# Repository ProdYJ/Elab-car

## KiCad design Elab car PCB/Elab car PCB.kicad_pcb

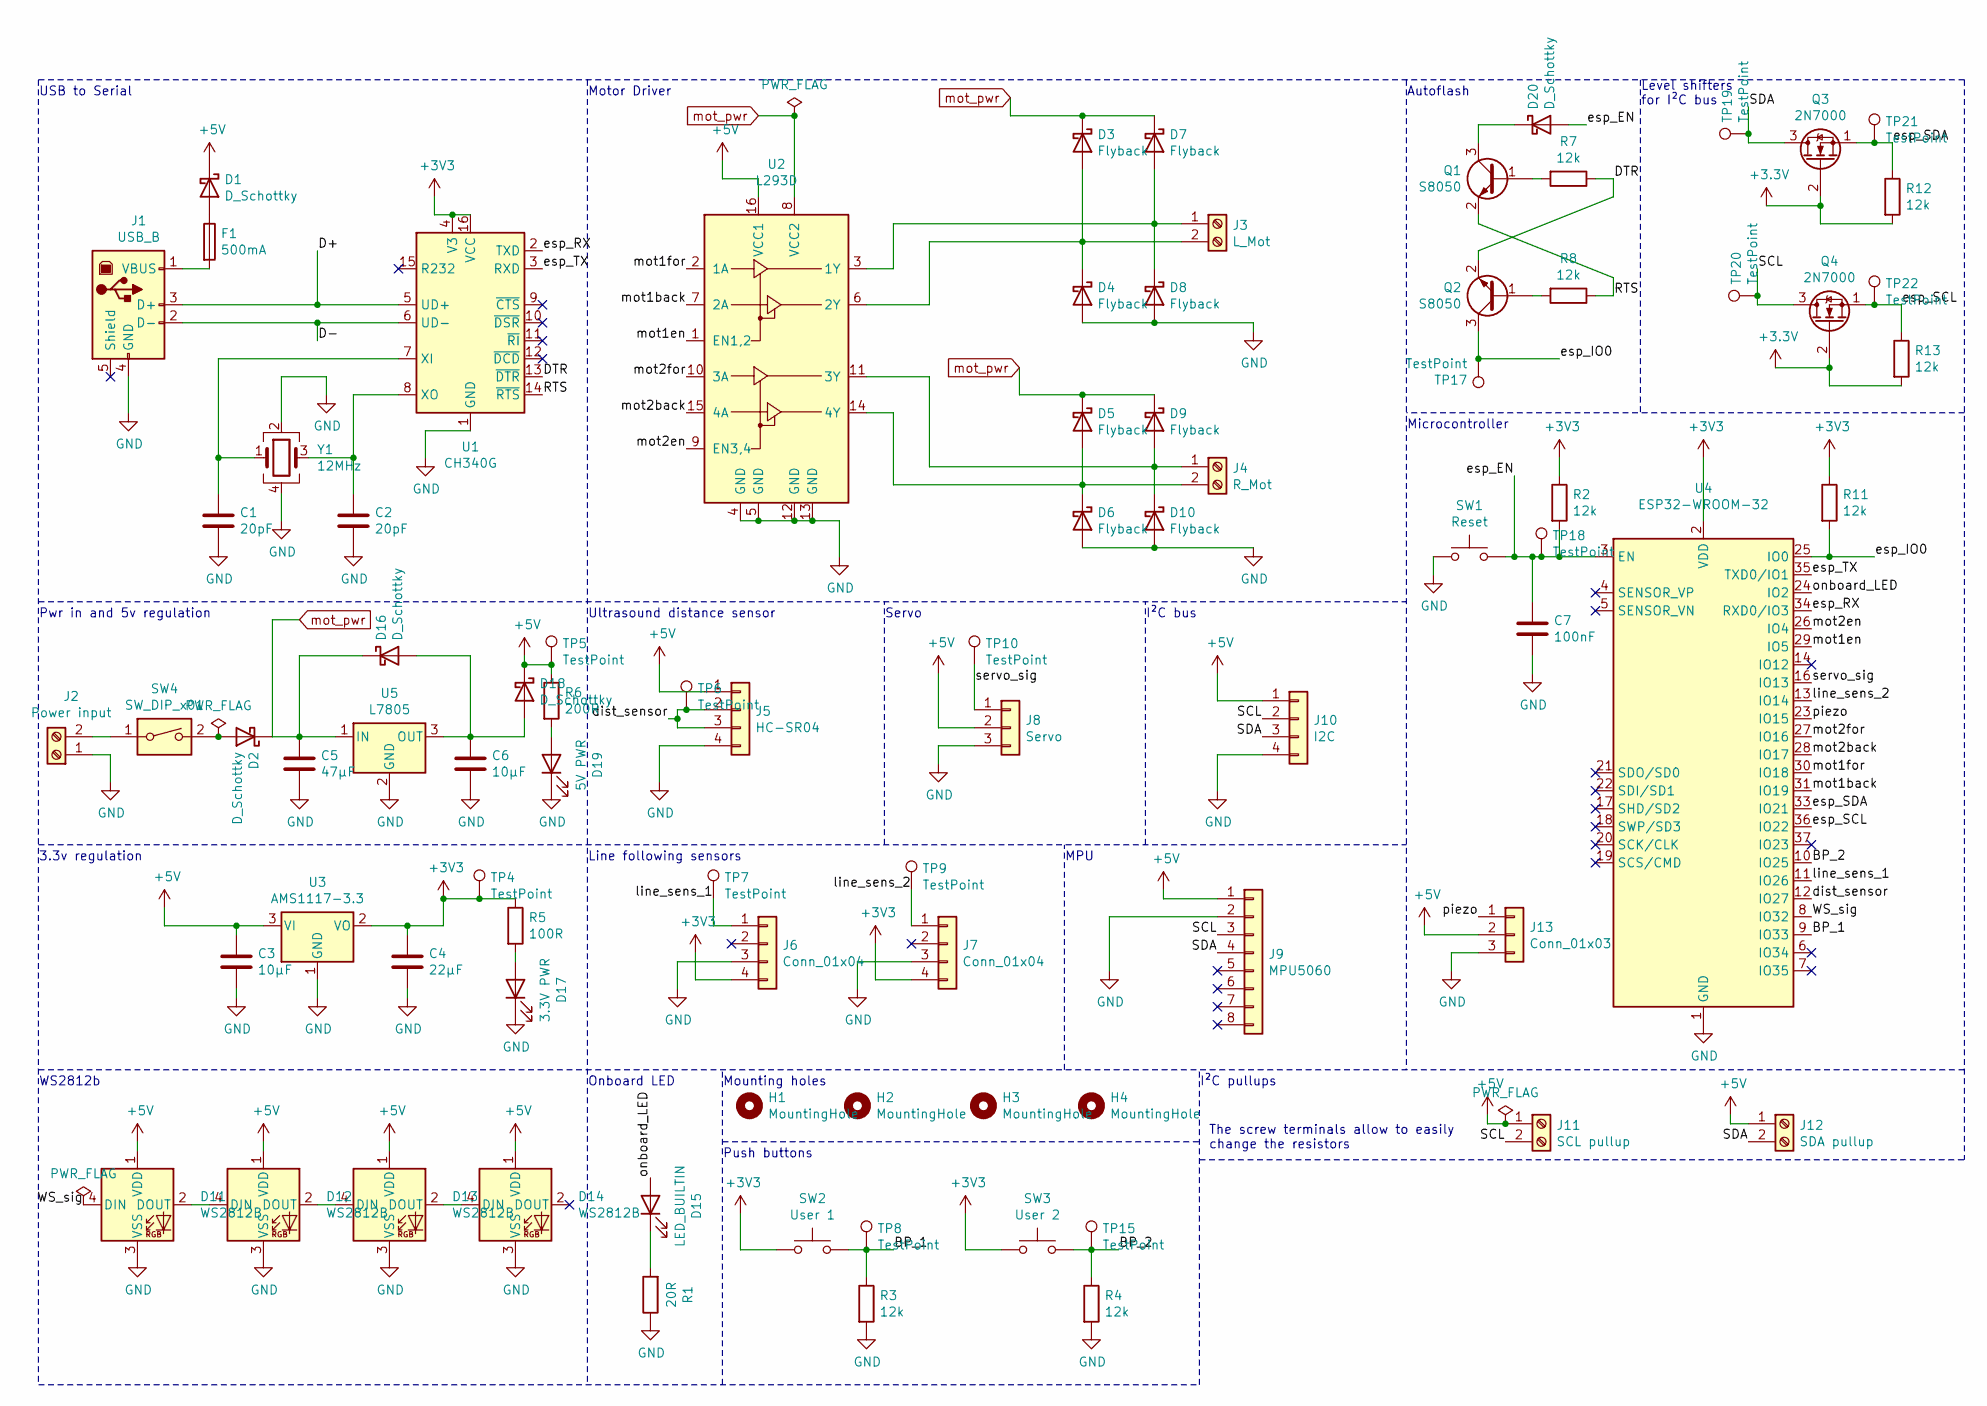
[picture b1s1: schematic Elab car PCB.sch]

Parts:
C1, C2: 20pF; C_1206_3216Metric_Pad1.33x1.80mm_HandSolder; LCSC # C1894
C3, C6: 10µF; CP_Elec_5x4.5; LCSC # C249788
C4: 22µF; CP_Elec_5x5.3; LCSC # C371125
C5: 47µF; CP_Elec_6.3x5.8; LCSC # C311639
C7: 100nF; C_1206_3216Metric_Pad1.33x1.80mm_HandSolder; LCSC # C107181
D1, D2, D16, D18, D20: D_Schottky; D_1206_3216Metric_Pad1.42x1.75mm_HandSolder; LCSC # C189958
D3, D4, D5, D6, D7, D8, D9, D10: Flyback; D_1206_3216Metric_Pad1.42x1.75mm_HandSolder; LCSC # C189958
D11, D12, D13, D14: WS2812B; LED_WS2812B_PLCC4_5.0x5.0mm_P3.2mm; LCSC # C114586
D15: LED_BUILTIN; LED_0805_2012Metric_Pad1.15x1.40mm_HandSolder; LCSC # C72035
D17: 3.3V PWR; LED_0805_2012Metric_Pad1.15x1.40mm_HandSolder; LCSC # C72035
D19: 5V PWR; LED_0805_2012Metric_Pad1.15x1.40mm_HandSolder; LCSC # C72035
F1: 500mA; Fuse_1206_3216Metric_Pad1.42x1.75mm_HandSolder; LCSC # C70070
H1, H2, H3, H4: MountingHole; MountingHole_3.2mm_M3_DIN965_Pad
J1: USB_B; USB_B_Lumberg_2411_02_Horizontal; LCSC # C397338
J2: Power input; TerminalBlock_bornier-2_P5.08mm; LCSC # C8465
J3: L_Mot; TerminalBlock_bornier-2_P5.08mm; LCSC # C8465
J4: R_Mot; TerminalBlock_bornier-2_P5.08mm; LCSC # C8465
J5: HC-SR04; PinHeader_1x04_P2.54mm_Vertical; LCSC # C124413
J6, J7: Conn_01x04; PinHeader_1x04_P2.54mm_Vertical
J8: Servo; PinHeader_1x03_P2.54mm_Vertical; LCSC # C225500
J9: MPU5060; PinHeader_1x08_P2.54mm_Vertical; LCSC # C27438
J10: I2C; PinHeader_1x04_P2.54mm_Vertical; LCSC # C124413
J11: SCL pullup; TerminalBlock_bornier-2_P5.08mm; LCSC # C8465
J12: SDA pullup; TerminalBlock_bornier-2_P5.08mm; LCSC # C8465
J13: Conn_01x03; PinHeader_1x03_P2.54mm_Vertical
Q1, Q2: S8050; SOT-23_Handsoldering
Q3, Q4: 2N7000; TO-92_Inline; LCSC # C9114
R1: 20R; R_1206_3216Metric_Pad1.30x1.75mm_HandSolder; LCSC # C25362
R2, R3, R4, R7, R8, R11, R12, R13: 12k; R_1206_3216Metric_Pad1.30x1.75mm_HandSolder; LCSC # C1491
R5: 100R; R_1206_3216Metric_Pad1.30x1.75mm_HandSolder; LCSC # C25362
R6: 200R; R_1206_3216Metric_Pad1.30x1.75mm_HandSolder; LCSC # C242479
SW1: Reset; SW_PUSH_6mm_H5mm; LCSC # C111373
SW2: User 1; SW_PUSH_6mm_H5mm; LCSC # C111373
SW3: User 2; SW_PUSH_6mm_H5mm; LCSC # C111373
SW4: SW_DIP_x01; SW_plugin8.5x8.5
TP4, TP5, TP6, TP7, TP8, TP9, TP10, TP15, TP17, TP18, TP19, TP20, TP21, TP22: TestPoint; TestPoint_Pad_D2.5mm
U1: CH340G; SOIC-16_3.9x9.9mm_P1.27mm; LCSC # C14267
U2: L293D; DIP-16_W7.62mm; LCSC # C12340
U3: AMS1117-3.3; SOT-223-3_TabPin2; LCSC # C369933
U4: ESP32-WROOM-32; LCSC # C473012
U5: L7805; TO-263-2; LCSC # C507146
Y1: 12MHz; Crystal_SMD_3225-4Pin_3.2x2.5mm_HandSoldering

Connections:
+5V: C3.1, D1.1 (K), D11.1 (VDD), D12.1 (VDD), D13.1 (VDD), D14.1 (VDD), D18.1 (K), J5.1, J8.2, J9.1, J10.1, J11.1, J12.1, J13.2, R6.1, TP5.1, U2.16 (VCC1), U3.3 (VI)
/BP_1: R3.1, SW2.2, TP8.1, U4.9 (IO33)
/BP_2: R4.1, SW3.2, TP15.1, U4.10 (IO25)
/D+: J1.3 (D+), U1.5 (UD+)
/D-: J1.2 (D-), U1.6 (UD-)
/DTR: Q2.2 (E), R7.1, U1.13 (~DTR)
/RTS: Q1.2 (E), R8.1, U1.14 (~RTS)
/SCL: J9.3, J10.2, J11.2, Q4.3 (D), TP20.1
/SDA: J9.4, J10.3, J12.2, Q3.3 (D), TP19.1
/WS_sig: D11.4 (DIN), U4.8 (IO32)
/dist_sensor: J5.2, J5.3, TP6.1, U4.12 (IO27)
/esp_EN: C7.1, D20.2 (A), R2.2, SW1.2, TP18.1, U4.3 (EN)
/esp_IO0: Q2.3 (C), R11.2, TP17.1, U4.25 (IO0)
/esp_RX: U1.2 (TXD), U4.34 (RXD0/IO3)
/esp_SCL: Q4.1 (S), R13.1, TP22.1, U4.36 (IO22)
/esp_SDA: Q3.1 (S), R12.1, TP21.1, U4.33 (IO21)
/esp_TX: U1.3 (RXD), U4.35 (TXD0/IO1)
/line_sens_1: J6.1, TP7.1, U4.11 (IO26)
/line_sens_2: J7.1, TP9.1, U4.13 (IO14)
/mot1back: U2.7 (2A), U4.31 (IO19)
/mot1en: U2.1 (EN1,2), U4.29 (IO5)
/mot1for: U2.2 (1A), U4.30 (IO18)
/mot2back: U2.15 (4A), U4.28 (IO17)
/mot2en: U2.9 (EN3,4), U4.26 (IO4)
/mot2for: U2.10 (3A), U4.27 (IO16)
/onboard_LED: D15.2 (A), U4.24 (IO2)
/piezo: J13.1, U4.23 (IO15)
/servo_sig: J8.1, TP10.1, U4.16 (IO13)
GND: C1.2, C2.2, C3.2, C4.2, C5.2, C6.2, C7.2, D4.2 (A), D6.2 (A), D8.2 (A), D10.2 (A), D11.3 (VSS), D12.3 (VSS), D13.3 (VSS), D14.3 (VSS), D17.1 (K), D19.1 (K), J1.4 (GND), J2.1, J5.4, J6.3, J7.3, J8.3, J9.2, J10.4, J13.3, R1.1, R3.2, R4.2, SW1.1, U1.1 (GND), U2.4 (GND), U2.5 (GND), U2.12 (GND), U2.13 (GND), U3.1 (GND), U4.1 (GND), U4.15 (GND), U4.38 (GND), U4.39 (GND), U5.2 (GND), Y1.2, Y1.4
unnamed: C1.1, U1.7 (XI), Y1.1
unnamed: C2.1, U1.8 (XO), Y1.3
unnamed: C6.1, D16.2 (A), D18.2 (A), U5.3 (OUT)
unnamed: D1.2 (A), F1.1
unnamed: D2.2 (A), SW4.2
unnamed: D3.2 (A), D4.1 (K), J3.2, U2.6 (2Y)
unnamed: D5.2 (A), D6.1 (K), J4.2, U2.14 (4Y)
unnamed: D7.2 (A), D8.1 (K), J3.1, U2.3 (1Y)
unnamed: D9.2 (A), D10.1 (K), J4.1, U2.11 (3Y)
unnamed: D11.2 (DOUT), D12.4 (DIN)
unnamed: D12.2 (DOUT), D13.4 (DIN)
unnamed: D13.2 (DOUT), D14.4 (DIN)
unnamed: D15.1 (K), R1.2
unnamed: D17.2 (A), R5.2
unnamed: D19.2 (A), R6.2
unnamed: D20.1 (K), Q1.3 (C)
unnamed: F1.2, J1.1 (VBUS)
unnamed: J2.2, SW4.1
unnamed: Q1.1 (B), R7.2
unnamed: Q2.1 (B), R8.2
mot_pwr: C5.1, D2.1 (K), D3.1 (K), D5.1 (K), D7.1 (K), D9.1 (K), D16.1 (K), U2.8 (VCC2), U5.1 (IN)

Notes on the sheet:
Ultrasound distance sensor
USB to Serial
Motor Driver
Pwr in and 5v regulation
3.3v regulation
WS2812b
Servo
I²C bus
Line following sensors
MPU
Onboard LED
Push buttons
I²C pullups
The screw terminals allow to easily change the resistors
Autoflash
Microcontroller
Level shifters for I²C bus
Mounting holes

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
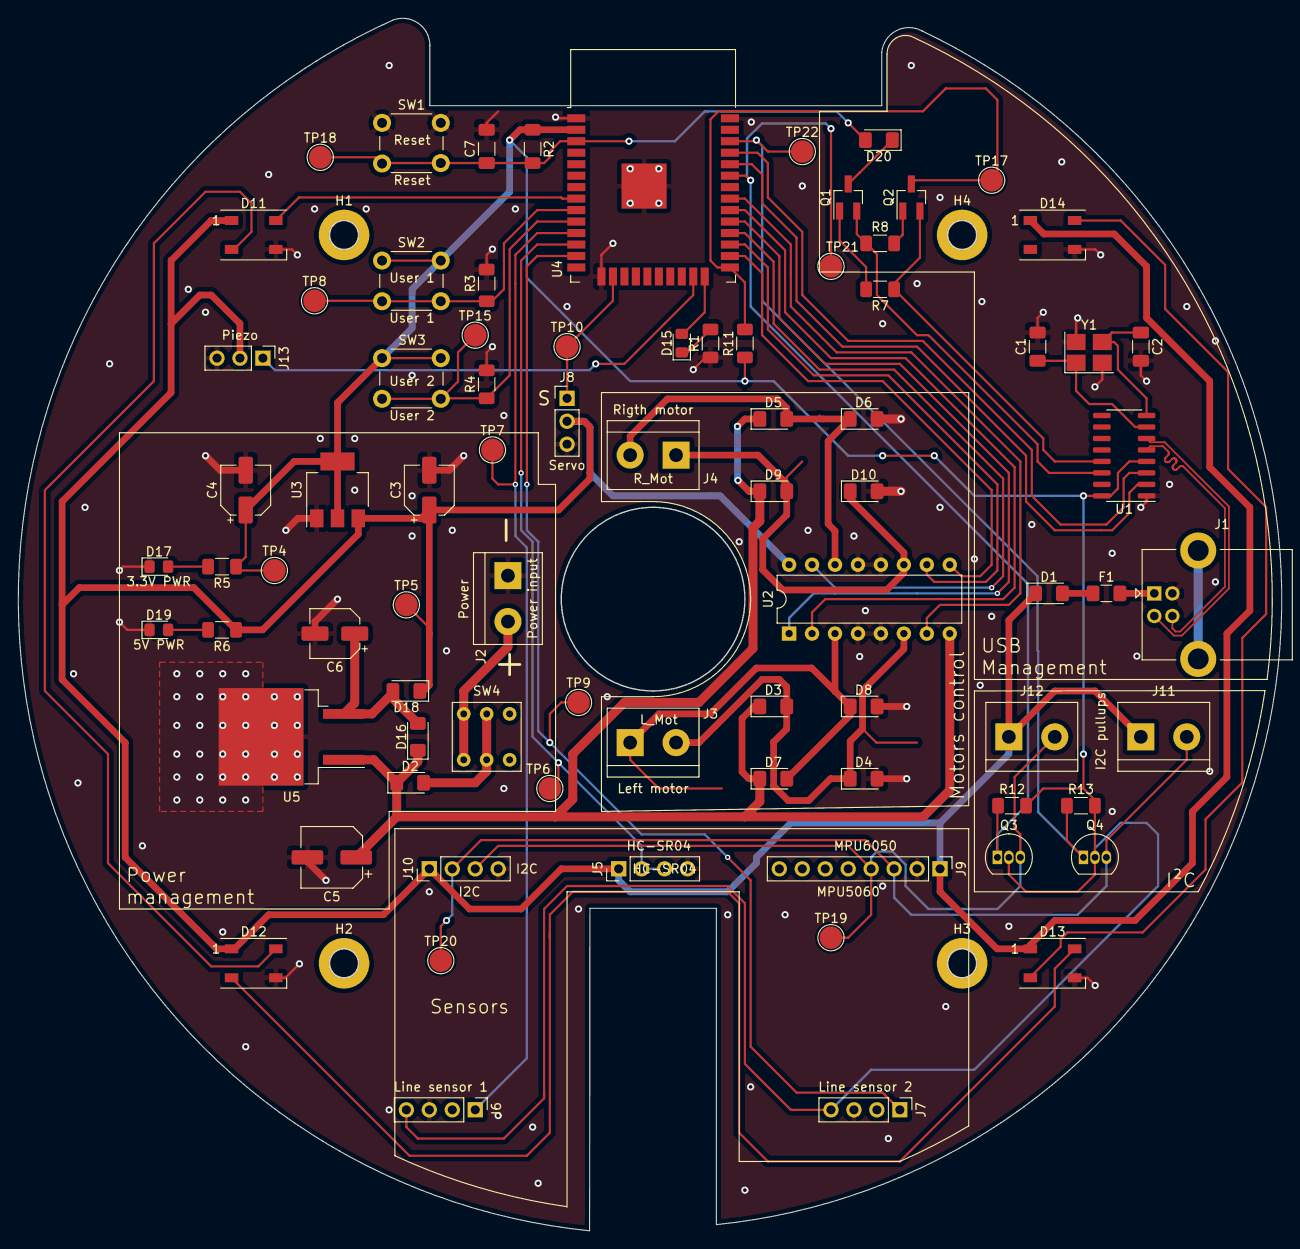
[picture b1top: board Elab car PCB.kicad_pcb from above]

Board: 2 copper layers, 139.8 x 134.2 mm, 84 parts (0 on the bottom side), 51 nets.

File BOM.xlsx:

Composant | Valeur | Références | Quantité
Capa | 20pF | C1, C2 | 2
Capa | 10µF | C3,C6 | 2 |  | Note: remplacé par capa 22µF pour tests
Capa | 22µF | C4 | 1
Capa | 47µF | C5 | 1
Capa | 100nF | C7 | 1
Diodes Shottky |  | D1, D2, D3, D4, D5, D6, D7, D8, D9, D10, D16, D18, D20 | 13
WS2812b |  | D11, D12, D13, D14 | 4
led beue |  | D15, D17, D19 | 3
Fusible | 500mA | F1 | 1
USB B receptacle |  | J1 | 1
Screw terminal | 1x2 P5,08 | J2, J3, J4, J11, J12 | 5 |  | Essayer d'en choper au 2067 comme un gros shlag ?
pin header | 1x4 P2,54 | J5, J10 | 2
pin header | 1x3 P2,54 | J6, J7, J8 | 3
pin header | 1x8 | J9 | 1 |  | note : remplacé par 2 connecteurs 1x4 pour les tests
BJT | S8050 | Q1, Q2 | 2
Mosfet | 2N7000 | Q3, Q4 | 2
Resistor | 20R | R5 | 1
Resistor | 85R | R1, R6 | 2
Resistor | 12k | R2, R3, R4, R7, R8, R11, R12, R13 | 8
Bpush Button | 6x6x5 | Sw1, Sw2, Sw3 | 3
CH340g |  | U1 | 1
TP |  |  | 22
L293D |  | U2 | 1
AMS1777-3,3 |  | U3 | 1
esp32-wroom-32D |  | U4 | 1
L7805 |  | U5 | 1
Crystal | 12MHz | Y1 | 1
 |  |  | 86

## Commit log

2021-03-24 Create LICENSE
2021-04-27 Assignation d'empreintes
2021-04-27 Ajout de références
2021-09-20 PCB creation
2021-09-21 Silk screen
2021-10-01 Esp32 design requirements corrections
2021-10-02 Board edge adjustment
2021-10-02 Front silk screen adjustment
2021-10-02 Adding gnd vias
2021-12-20 V1.1
2021-12-20 Little corrections of V1.1
